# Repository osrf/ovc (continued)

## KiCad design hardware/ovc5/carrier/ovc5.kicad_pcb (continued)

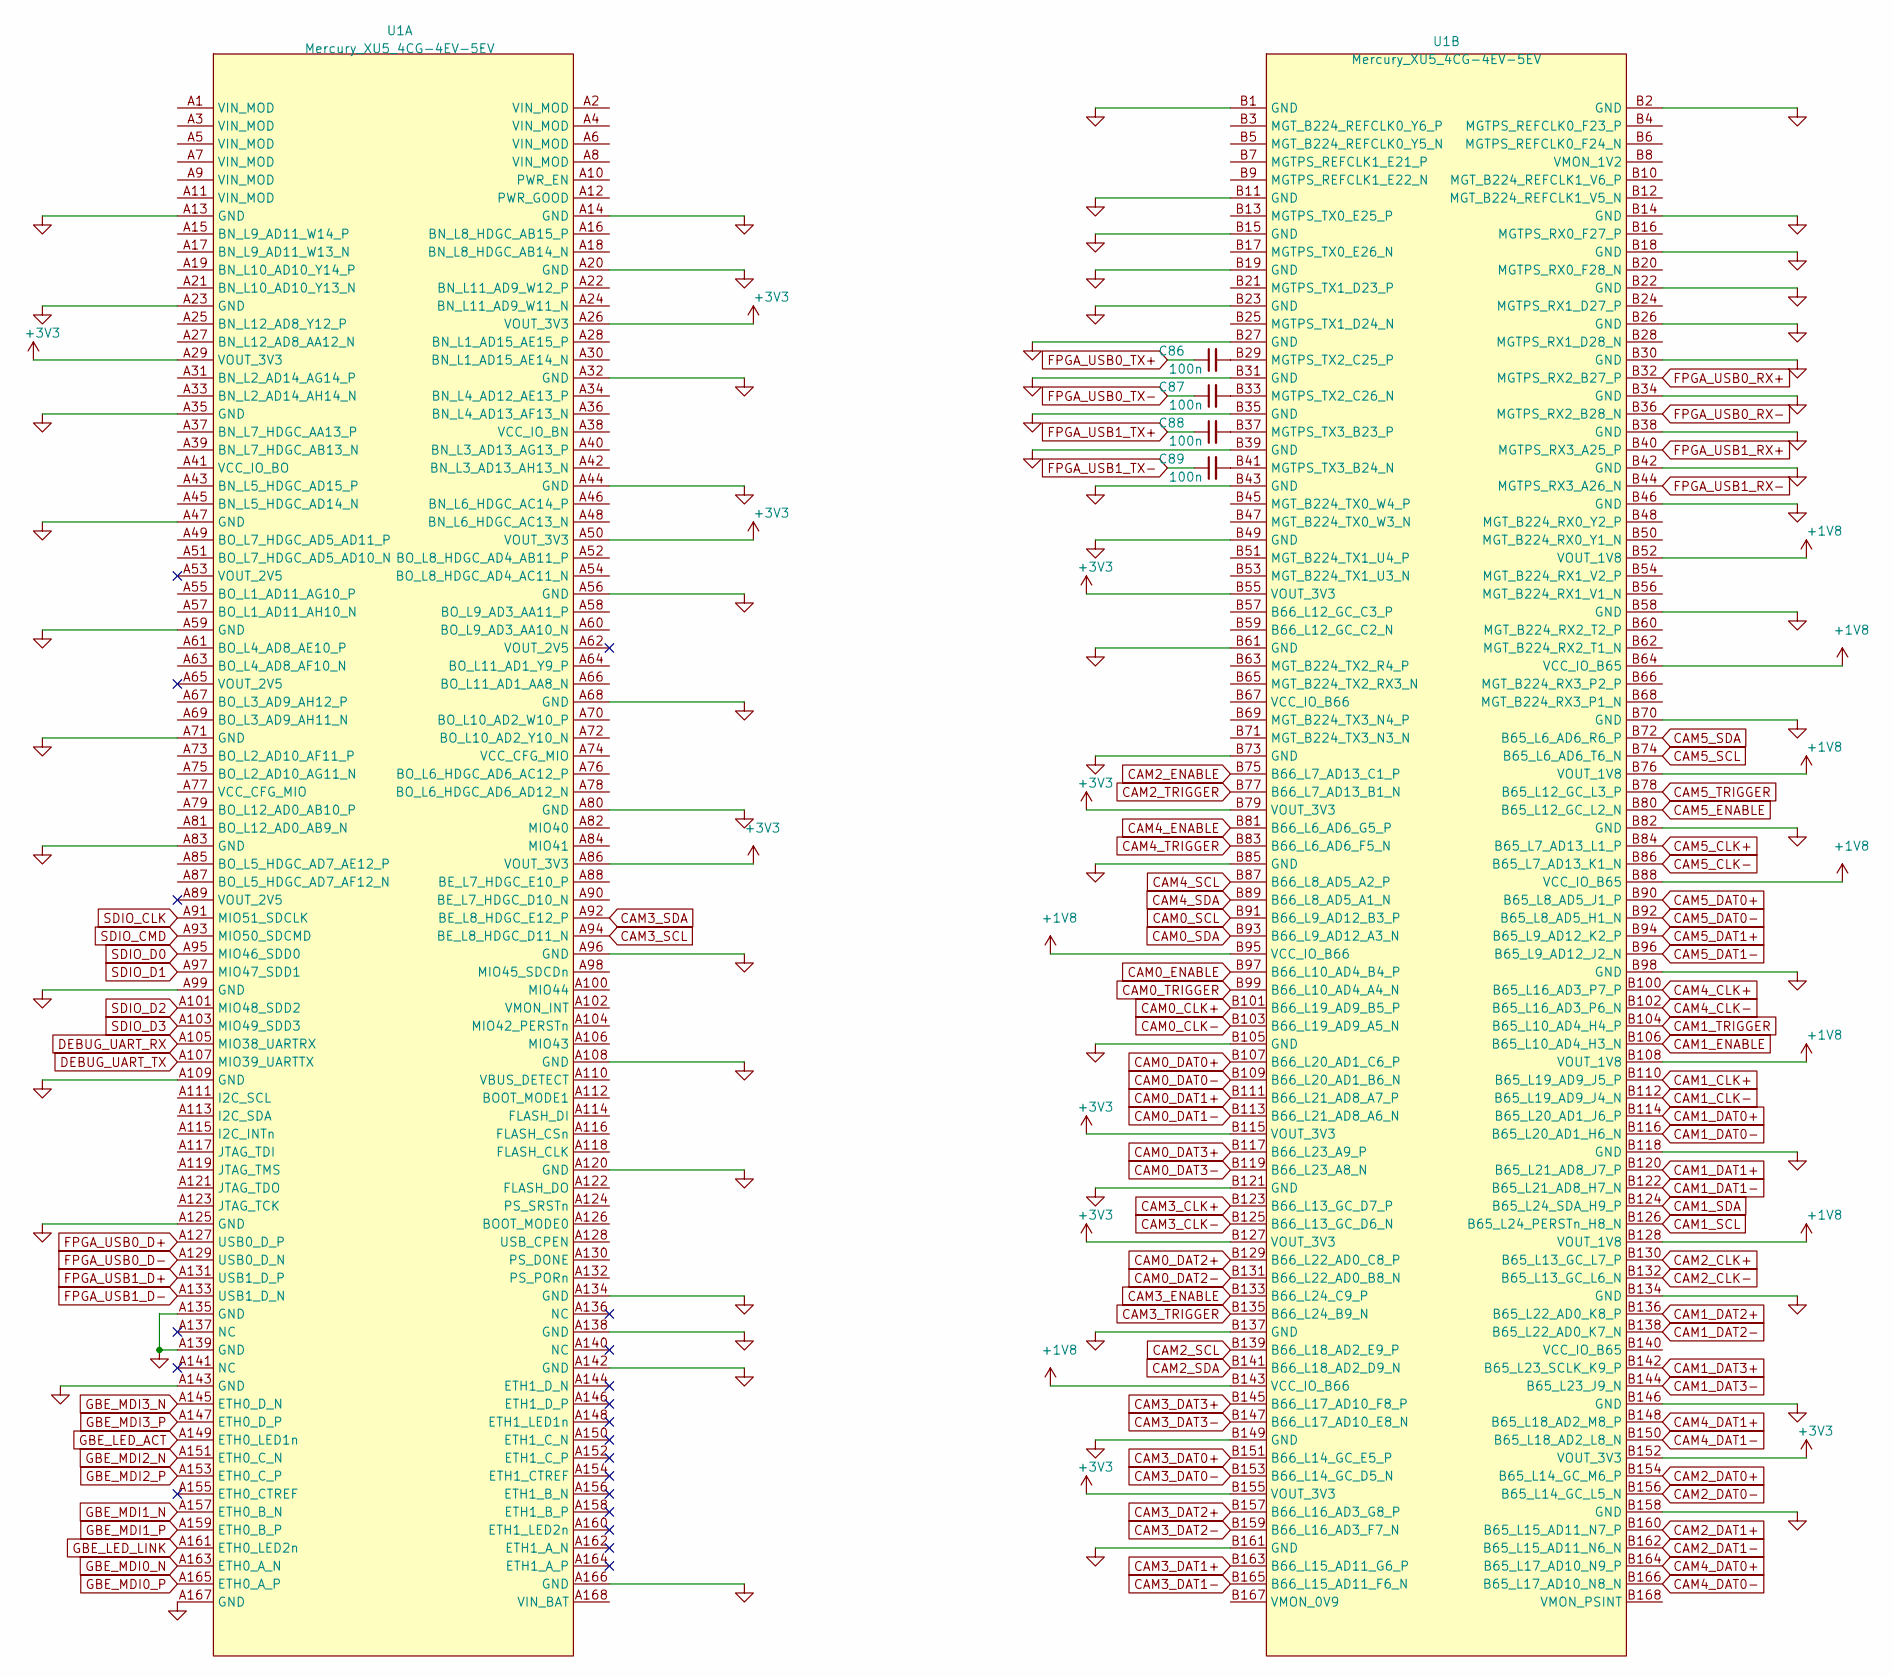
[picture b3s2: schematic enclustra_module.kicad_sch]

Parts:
C86, C87, C88, C89: 100n; C_0402_1005Metric
U1: Mercury_XU5_4CG-4EV-5EV; Mercury_XU5

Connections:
+1V8: U1.B52 (VOUT_1V8), U1.B64 (VCC_IO_B65), U1.B76 (VOUT_1V8), U1.B88 (VCC_IO_B65), U1.B95 (VCC_IO_B66), U1.B108 (VOUT_1V8), U1.B128 (VOUT_1V8), U1.B143 (VCC_IO_B66); also elsewhere on the board
+3V3: U1.A26 (VOUT_3V3), U1.A29 (VOUT_3V3), U1.A50 (VOUT_3V3), U1.A86 (VOUT_3V3), U1.B55 (VOUT_3V3), U1.B79 (VOUT_3V3), U1.B115 (VOUT_3V3), U1.B127 (VOUT_3V3), U1.B152 (VOUT_3V3), U1.B155 (VOUT_3V3); also elsewhere on the board
CAM0_CLK+: U1.B101 (B66_L19_AD9_B5_P); also elsewhere on the board
CAM0_CLK-: U1.B103 (B66_L19_AD9_A5_N); also elsewhere on the board
CAM0_DAT0+: U1.B107 (B66_L20_AD1_C6_P); also elsewhere on the board
CAM0_DAT0-: U1.B109 (B66_L20_AD1_B6_N); also elsewhere on the board
CAM0_DAT1+: U1.B111 (B66_L21_AD8_A7_P); also elsewhere on the board
CAM0_DAT1-: U1.B113 (B66_L21_AD8_A6_N); also elsewhere on the board
CAM0_DAT2+: U1.B129 (B66_L22_AD0_C8_P); also elsewhere on the board
CAM0_DAT2-: U1.B131 (B66_L22_AD0_B8_N); also elsewhere on the board
CAM0_DAT3+: U1.B117 (B66_L23_A9_P); also elsewhere on the board
CAM0_DAT3-: U1.B119 (B66_L23_A8_N); also elsewhere on the board
CAM0_ENABLE: U1.B97 (B66_L10_AD4_B4_P); also elsewhere on the board
CAM0_SCL: U1.B91 (B66_L9_AD12_B3_P); also elsewhere on the board
CAM0_SDA: U1.B93 (B66_L9_AD12_A3_N); also elsewhere on the board
CAM0_TRIGGER: U1.B99 (B66_L10_AD4_A4_N); also elsewhere on the board
CAM1_CLK+: U1.B110 (B65_L19_AD9_J5_P); also elsewhere on the board
CAM1_CLK-: U1.B112 (B65_L19_AD9_J4_N); also elsewhere on the board
CAM1_DAT0+: U1.B114 (B65_L20_AD1_J6_P); also elsewhere on the board
CAM1_DAT0-: U1.B116 (B65_L20_AD1_H6_N); also elsewhere on the board
CAM1_DAT1+: U1.B120 (B65_L21_AD8_J7_P); also elsewhere on the board
CAM1_DAT1-: U1.B122 (B65_L21_AD8_H7_N); also elsewhere on the board
CAM1_DAT2+: U1.B136 (B65_L22_AD0_K8_P); also elsewhere on the board
CAM1_DAT2-: U1.B138 (B65_L22_AD0_K7_N); also elsewhere on the board
CAM1_DAT3+: U1.B142 (B65_L23_SCLK_K9_P); also elsewhere on the board
CAM1_DAT3-: U1.B144 (B65_L23_J9_N); also elsewhere on the board
CAM1_ENABLE: U1.B106 (B65_L10_AD4_H3_N); also elsewhere on the board
CAM1_SCL: U1.B126 (B65_L24_PERSTn_H8_N); also elsewhere on the board
CAM1_SDA: U1.B124 (B65_L24_SDA_H9_P); also elsewhere on the board
CAM1_TRIGGER: U1.B104 (B65_L10_AD4_H4_P); also elsewhere on the board
CAM2_CLK+: U1.B130 (B65_L13_GC_L7_P); also elsewhere on the board
CAM2_CLK-: U1.B132 (B65_L13_GC_L6_N); also elsewhere on the board
CAM2_DAT0+: U1.B154 (B65_L14_GC_M6_P); also elsewhere on the board
CAM2_DAT0-: U1.B156 (B65_L14_GC_L5_N); also elsewhere on the board
CAM2_DAT1+: U1.B160 (B65_L15_AD11_N7_P); also elsewhere on the board
CAM2_DAT1-: U1.B162 (B65_L15_AD11_N6_N); also elsewhere on the board
CAM2_ENABLE: U1.B75 (B66_L7_AD13_C1_P); also elsewhere on the board
CAM2_SCL: U1.B139 (B66_L18_AD2_E9_P); also elsewhere on the board
CAM2_SDA: U1.B141 (B66_L18_AD2_D9_N); also elsewhere on the board
CAM2_TRIGGER: U1.B77 (B66_L7_AD13_B1_N); also elsewhere on the board
CAM3_CLK+: U1.B123 (B66_L13_GC_D7_P); also elsewhere on the board
CAM3_CLK-: U1.B125 (B66_L13_GC_D6_N); also elsewhere on the board
CAM3_DAT0+: U1.B151 (B66_L14_GC_E5_P); also elsewhere on the board
CAM3_DAT0-: U1.B153 (B66_L14_GC_D5_N); also elsewhere on the board
CAM3_DAT1+: U1.B163 (B66_L15_AD11_G6_P); also elsewhere on the board
CAM3_DAT1-: U1.B165 (B66_L15_AD11_F6_N); also elsewhere on the board
CAM3_DAT2+: U1.B157 (B66_L16_AD3_G8_P); also elsewhere on the board
CAM3_DAT2-: U1.B159 (B66_L16_AD3_F7_N); also elsewhere on the board
CAM3_DAT3+: U1.B145 (B66_L17_AD10_F8_P); also elsewhere on the board
CAM3_DAT3-: U1.B147 (B66_L17_AD10_E8_N); also elsewhere on the board
CAM3_ENABLE: U1.B133 (B66_L24_C9_P); also elsewhere on the board
CAM3_SCL: U1.A94 (BE_L8_HDGC_D11_N); also elsewhere on the board
CAM3_SDA: U1.A92 (BE_L8_HDGC_E12_P); also elsewhere on the board
CAM3_TRIGGER: U1.B135 (B66_L24_B9_N); also elsewhere on the board
CAM4_CLK+: U1.B100 (B65_L16_AD3_P7_P); also elsewhere on the board
CAM4_CLK-: U1.B102 (B65_L16_AD3_P6_N); also elsewhere on the board
CAM4_DAT0+: U1.B164 (B65_L17_AD10_N9_P); also elsewhere on the board
CAM4_DAT0-: U1.B166 (B65_L17_AD10_N8_N); also elsewhere on the board
CAM4_DAT1+: U1.B148 (B65_L18_AD2_M8_P); also elsewhere on the board
CAM4_DAT1-: U1.B150 (B65_L18_AD2_L8_N); also elsewhere on the board
CAM4_ENABLE: U1.B81 (B66_L6_AD6_G5_P); also elsewhere on the board
CAM4_SCL: U1.B87 (B66_L8_AD5_A2_P); also elsewhere on the board
CAM4_SDA: U1.B89 (B66_L8_AD5_A1_N); also elsewhere on the board
CAM4_TRIGGER: U1.B83 (B66_L6_AD6_F5_N); also elsewhere on the board
CAM5_CLK+: U1.B84 (B65_L7_AD13_L1_P); also elsewhere on the board
CAM5_CLK-: U1.B86 (B65_L7_AD13_K1_N); also elsewhere on the board
CAM5_DAT0+: U1.B90 (B65_L8_AD5_J1_P); also elsewhere on the board
CAM5_DAT0-: U1.B92 (B65_L8_AD5_H1_N); also elsewhere on the board
CAM5_DAT1+: U1.B94 (B65_L9_AD12_K2_P); also elsewhere on the board
CAM5_DAT1-: U1.B96 (B65_L9_AD12_J2_N); also elsewhere on the board
CAM5_ENABLE: U1.B80 (B65_L12_GC_L2_N); also elsewhere on the board
CAM5_SCL: U1.B74 (B65_L6_AD6_T6_N); also elsewhere on the board
CAM5_SDA: U1.B72 (B65_L6_AD6_R6_P); also elsewhere on the board
CAM5_TRIGGER: U1.B78 (B65_L12_GC_L3_P); also elsewhere on the board
DEBUG_UART_RX: U1.A105 (MIO38_UARTRX); also elsewhere on the board
DEBUG_UART_TX: U1.A107 (MIO39_UARTTX); also elsewhere on the board
FPGA_USB0_D+: U1.A127 (USB0_D_P); also elsewhere on the board
FPGA_USB0_D-: U1.A129 (USB0_D_N); also elsewhere on the board
FPGA_USB0_RX+: U1.B32 (MGTPS_RX2_B27_P); also elsewhere on the board
FPGA_USB0_RX-: U1.B36 (MGTPS_RX2_B28_N); also elsewhere on the board
FPGA_USB0_TX+: C86.1; also elsewhere on the board
FPGA_USB0_TX-: C87.1; also elsewhere on the board
FPGA_USB1_D+: U1.A131 (USB1_D_P); also elsewhere on the board
FPGA_USB1_D-: U1.A133 (USB1_D_N); also elsewhere on the board
FPGA_USB1_RX+: U1.B40 (MGTPS_RX3_A25_P); also elsewhere on the board
FPGA_USB1_RX-: U1.B44 (MGTPS_RX3_A26_N); also elsewhere on the board
FPGA_USB1_TX+: C88.1; also elsewhere on the board
FPGA_USB1_TX-: C89.1; also elsewhere on the board
GBE_LED_ACT: U1.A149 (ETH0_LED1n); also elsewhere on the board
GBE_LED_LINK: U1.A161 (ETH0_LED2n); also elsewhere on the board
GBE_MDI0_N: U1.A163 (ETH0_A_N); also elsewhere on the board
GBE_MDI0_P: U1.A165 (ETH0_A_P); also elsewhere on the board
GBE_MDI1_N: U1.A157 (ETH0_B_N); also elsewhere on the board
GBE_MDI1_P: U1.A159 (ETH0_B_P); also elsewhere on the board
GBE_MDI2_N: U1.A151 (ETH0_C_N); also elsewhere on the board
GBE_MDI2_P: U1.A153 (ETH0_C_P); also elsewhere on the board
GBE_MDI3_N: U1.A145 (ETH0_D_N); also elsewhere on the board
GBE_MDI3_P: U1.A147 (ETH0_D_P); also elsewhere on the board
GND: U1.A13 (GND), U1.A14 (GND), U1.A20 (GND), U1.A23 (GND), U1.A32 (GND), U1.A35 (GND), U1.A44 (GND), U1.A47 (GND), U1.A56 (GND), U1.A59 (GND), U1.A68 (GND), U1.A71 (GND), U1.A80 (GND), U1.A83 (GND), U1.A96 (GND), U1.A99 (GND), U1.A108 (GND), U1.A109 (GND), U1.A120 (GND), U1.A125 (GND), U1.A134 (GND), U1.A135 (GND), U1.A138 (GND), U1.A139 (GND), U1.A142 (GND), U1.A143 (GND), U1.A166 (GND), U1.A167 (GND), U1.B1 (GND), U1.B2 (GND), U1.B11 (GND), U1.B14 (GND), U1.B15 (GND), U1.B18 (GND), U1.B19 (GND), U1.B22 (GND), U1.B23 (GND), U1.B26 (GND), U1.B27 (GND), U1.B30 (GND), U1.B31 (GND), U1.B34 (GND), U1.B35 (GND), U1.B38 (GND), U1.B39 (GND), U1.B42 (GND), U1.B43 (GND), U1.B46 (GND), U1.B49 (GND), U1.B58 (GND), U1.B61 (GND), U1.B70 (GND), U1.B73 (GND), U1.B82 (GND), U1.B85 (GND), U1.B98 (GND), U1.B105 (GND), U1.B118 (GND), U1.B121 (GND), U1.B134 (GND), U1.B137 (GND), U1.B146 (GND), U1.B149 (GND), U1.B158 (GND), U1.B161 (GND); also elsewhere on the board
unnamed: C86.2, U1.B29 (MGTPS_TX2_C25_P)
unnamed: C87.2, U1.B33 (MGTPS_TX2_C26_N)
unnamed: C88.2, U1.B37 (MGTPS_TX3_B23_P)
unnamed: C89.2, U1.B41 (MGTPS_TX3_B24_N)
SDIO_CLK: U1.A91 (MIO51_SDCLK); also elsewhere on the board
SDIO_CMD: U1.A93 (MIO50_SDCMD); also elsewhere on the board
SDIO_D0: U1.A95 (MIO46_SDD0); also elsewhere on the board
SDIO_D1: U1.A97 (MIO47_SDD1); also elsewhere on the board
SDIO_D2: U1.A101 (MIO48_SDD2); also elsewhere on the board
SDIO_D3: U1.A103 (MIO49_SDD3); also elsewhere on the board

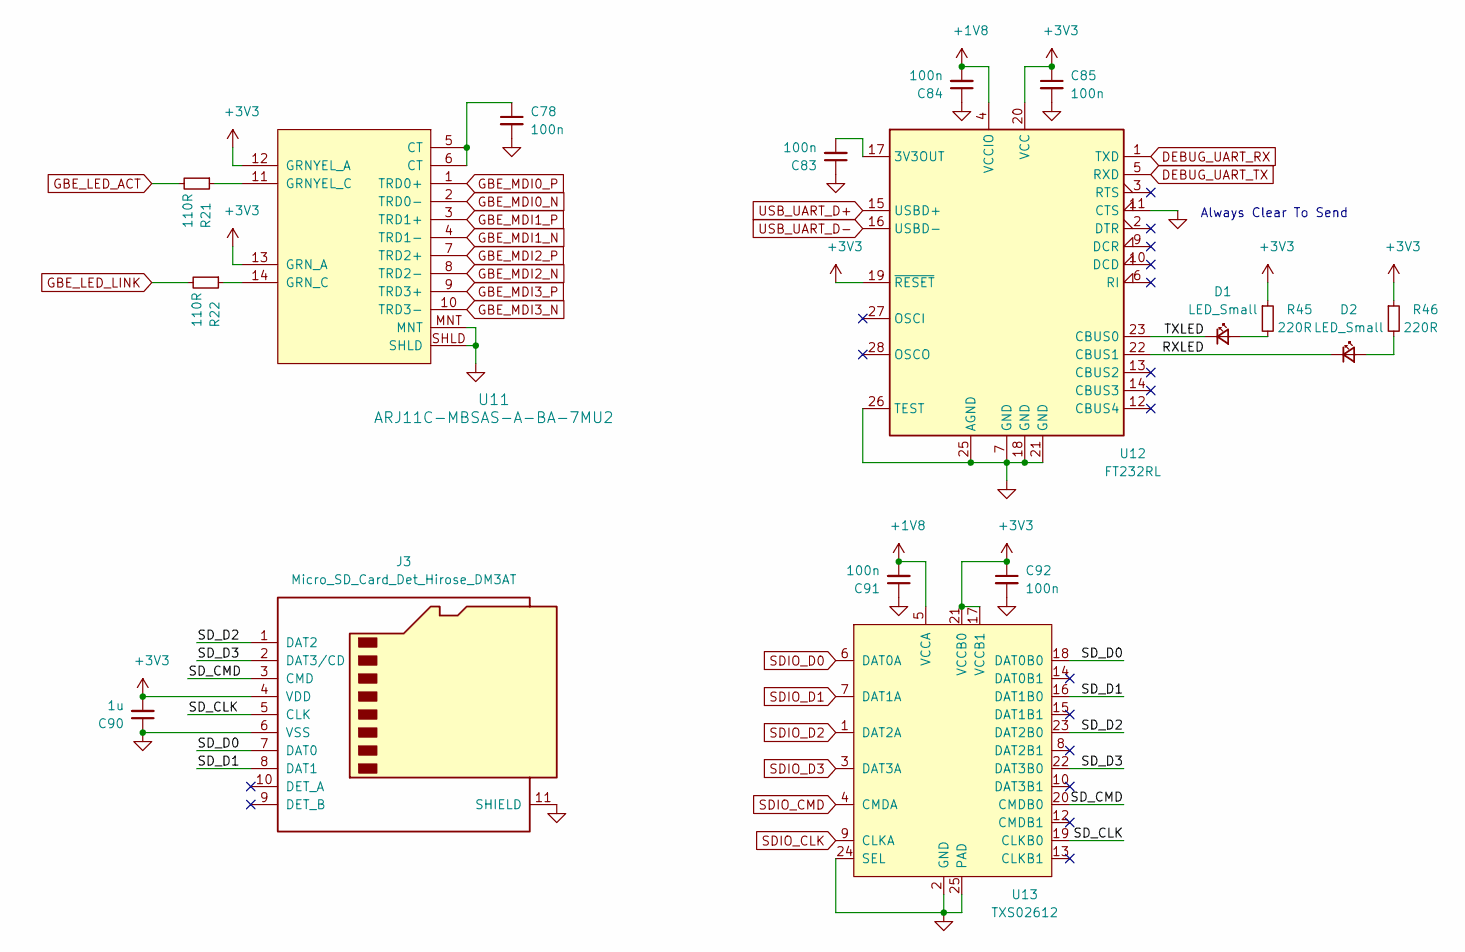
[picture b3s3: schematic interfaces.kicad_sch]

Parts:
C78, C83, C84, C85, C91, C92: 100n; C_0402_1005Metric
C90: 1u; C_0402_1005Metric
D1, D2: LED_Small; LED_0402_1005Metric
J3: Micro_SD_Card_Det_Hirose_DM3AT; microSD_HC_Hirose_DM3AT-SF-PEJM5
R21, R22: 110R; R_0603_1608Metric
R45, R46: 220R; R_0402_1005Metric
U11: ARJ11C-MBSAS-A-BA-7MU2
U12: FT232RL; SSOP-28_5.3x10.2mm_P0.65mm
U13: TXS02612; TI_RTW0024B

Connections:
+1V8: C84.2, C91.2, U12.4 (VCCIO), U13.5 (VCCA); also elsewhere on the board
+3V3: C85.1, C90.2, C92.1, J3.4 (VDD), R45.1, R46.1, U11.12 (GRNYEL_A), U11.13 (GRN_A), U12.19 (~RESET~), U12.20 (VCC), U13.17 (VCCB1), U13.21 (VCCB0); also elsewhere on the board
/Interfaces/RXLED: D2.1 (K), U12.22 (CBUS1)
/Interfaces/SD_CLK: J3.5 (CLK), U13.19 (CLKB0)
/Interfaces/SD_CMD: J3.3 (CMD), U13.20 (CMDB0)
/Interfaces/SD_D0: J3.7 (DAT0), U13.18 (DAT0B0)
/Interfaces/SD_D1: J3.8 (DAT1), U13.16 (DAT1B0)
/Interfaces/SD_D2: J3.1 (DAT2), U13.23 (DAT2B0)
/Interfaces/SD_D3: J3.2 (DAT3/CD), U13.22 (DAT3B0)
/Interfaces/TXLED: D1.1 (K), U12.23 (CBUS0)
DEBUG_UART_RX: U12.1 (TXD); also elsewhere on the board
DEBUG_UART_TX: U12.5 (RXD); also elsewhere on the board
GBE_LED_ACT: R21.2; also elsewhere on the board
GBE_LED_LINK: R22.2; also elsewhere on the board
GBE_MDI0_N: U11.2 (TRD0-); also elsewhere on the board
GBE_MDI0_P: U11.1 (TRD0+); also elsewhere on the board
GBE_MDI1_N: U11.4 (TRD1-); also elsewhere on the board
GBE_MDI1_P: U11.3 (TRD1+); also elsewhere on the board
GBE_MDI2_N: U11.8 (TRD2-); also elsewhere on the board
GBE_MDI2_P: U11.7 (TRD2+); also elsewhere on the board
GBE_MDI3_N: U11.10 (TRD3-); also elsewhere on the board
GBE_MDI3_P: U11.9 (TRD3+); also elsewhere on the board
GND: C78.2, C83.1, C84.1, C85.2, C90.1, C91.1, C92.2, J3.6 (VSS), J3.11 (SHIELD), U11.MNT, U11.SHLD, U12.7 (GND), U12.11 (CTS), U12.18 (GND), U12.21 (GND), U12.25 (AGND), U12.26 (TEST), U13.2 (GND), U13.11 (GND), U13.24 (SEL), U13.25 (PAD); also elsewhere on the board
unnamed: C78.1, U11.5 (CT), U11.6 (CT)
unnamed: C83.2, U12.17 (3V3OUT)
unnamed: D1.2 (A), R45.2
unnamed: D2.2 (A), R46.2
unnamed: R21.1, U11.11 (GRNYEL_C)
unnamed: R22.1, U11.14 (GRN_C)
SDIO_CLK: U13.9 (CLKA); also elsewhere on the board
SDIO_CMD: U13.4 (CMDA); also elsewhere on the board
SDIO_D0: U13.6 (DAT0A); also elsewhere on the board
SDIO_D1: U13.7 (DAT1A); also elsewhere on the board
SDIO_D2: U13.1 (DAT2A); also elsewhere on the board
SDIO_D3: U13.3 (DAT3A); also elsewhere on the board
USB_UART_D+: U12.15 (USBD+); also elsewhere on the board
USB_UART_D-: U12.16 (USBD-); also elsewhere on the board

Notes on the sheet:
Always Clear To Send

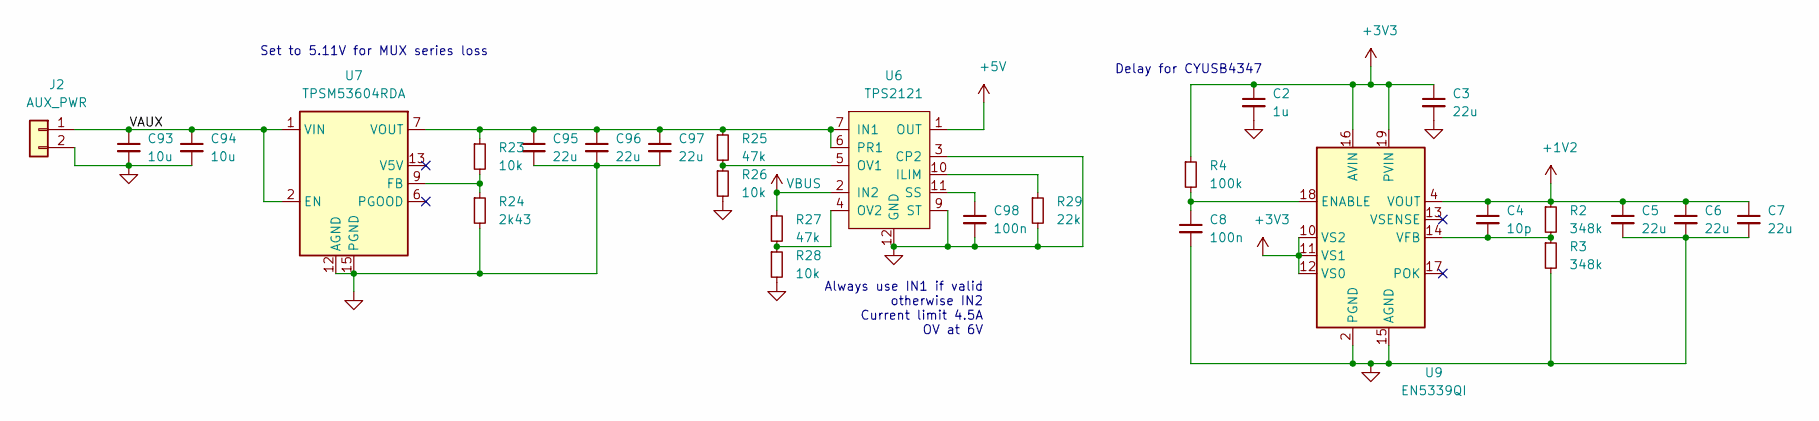
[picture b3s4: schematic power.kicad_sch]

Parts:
C2: 1u; C_0402_1005Metric
C3, C5, C6, C7, C95, C96, C97: 22u; C_0603_1608Metric
C4: 10p; C_0402_1005Metric
C8, C98: 100n; C_0402_1005Metric
C93, C94: 10u; C_1206_3216Metric
J2: AUX_PWR; Molex_Nano-Fit_105313-xx02_1x02_P2.50mm_Horizontal
R2, R3: 348k; R_0402_1005Metric
R4: 100k; R_0402_1005Metric
R23, R26, R28: 10k; R_0402_1005Metric
R24: 2k43; R_0402_1005Metric
R25, R27: 47k; R_0402_1005Metric
R29: 22k; R_0402_1005Metric
U6: TPS2121; Texas_VQFN-HR-12_2x2.5_Pitch0.5mm
U7: TPSM53604RDA; Texas_B3QFN-14-1EP_5x5.5mm_P0.65mm_ThermalVia
U9: EN5339QI; Converter_DCDC_Intel_QFN-24_4x6mm_P0.65mm_ThermalVias

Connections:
+1V2: C4.1, C5.1, C6.1, C7.1, R2.1, U9.4 (VOUT), U9.5 (VOUT), U9.6 (VOUT), U9.7 (VOUT); also elsewhere on the board
+3V3: C2.1, C3.1, R4.1, U9.10 (VS2), U9.11 (VS1), U9.12 (VS0), U9.16 (AVIN), U9.19 (PVIN), U9.20 (PVIN); also elsewhere on the board
+5V: U6.1 (OUT), U6.8 (OUT); also elsewhere on the board
/Power/VAUX: C93.1, C94.1, J2.1, U7.1 (VIN), U7.2 (EN), U7.14 (VIN)
GND: C2.2, C3.2, C5.2, C6.2, C7.2, C8.2, C93.2, C94.2, C95.2, C96.2, C97.2, C98.2, J2.2, R3.2, R24.2, R26.2, R28.2, R29.2, U6.3 (CP2), U6.9 (ST), U6.12 (GND), U7.3 (PGND), U7.10 (PGND), U7.11 (PGND), U7.12 (AGND), U7.15 (PGND), U9.2 (PGND), U9.3 (PGND), U9.8 (PGND), U9.9 (PGND), U9.15 (AGND), U9.25 (PGND); also elsewhere on the board
unnamed: C4.2, R2.2, R3.1, U9.14 (VFB)
unnamed: C8.1, R4.2, U9.18 (ENABLE)
unnamed: C95.1, C96.1, C97.1, R23.1, R25.1, U6.6 (PR1), U6.7 (IN1), U7.7 (VOUT), U7.8 (VOUT)
unnamed: C98.1, U6.11 (SS)
unnamed: R23.2, R24.1, U7.9 (FB)
unnamed: R25.2, R26.1, U6.5 (OV1)
unnamed: R27.2, R28.1, U6.4 (OV2)
unnamed: R29.1, U6.10 (ILIM)
VBUS: R27.1, U6.2 (IN2); also elsewhere on the board

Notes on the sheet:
Set to 5.11V for MUX series loss
Always use IN1 if valid otherwise IN2 Current limit 4.5A OV at 6V
Delay for CYUSB4347

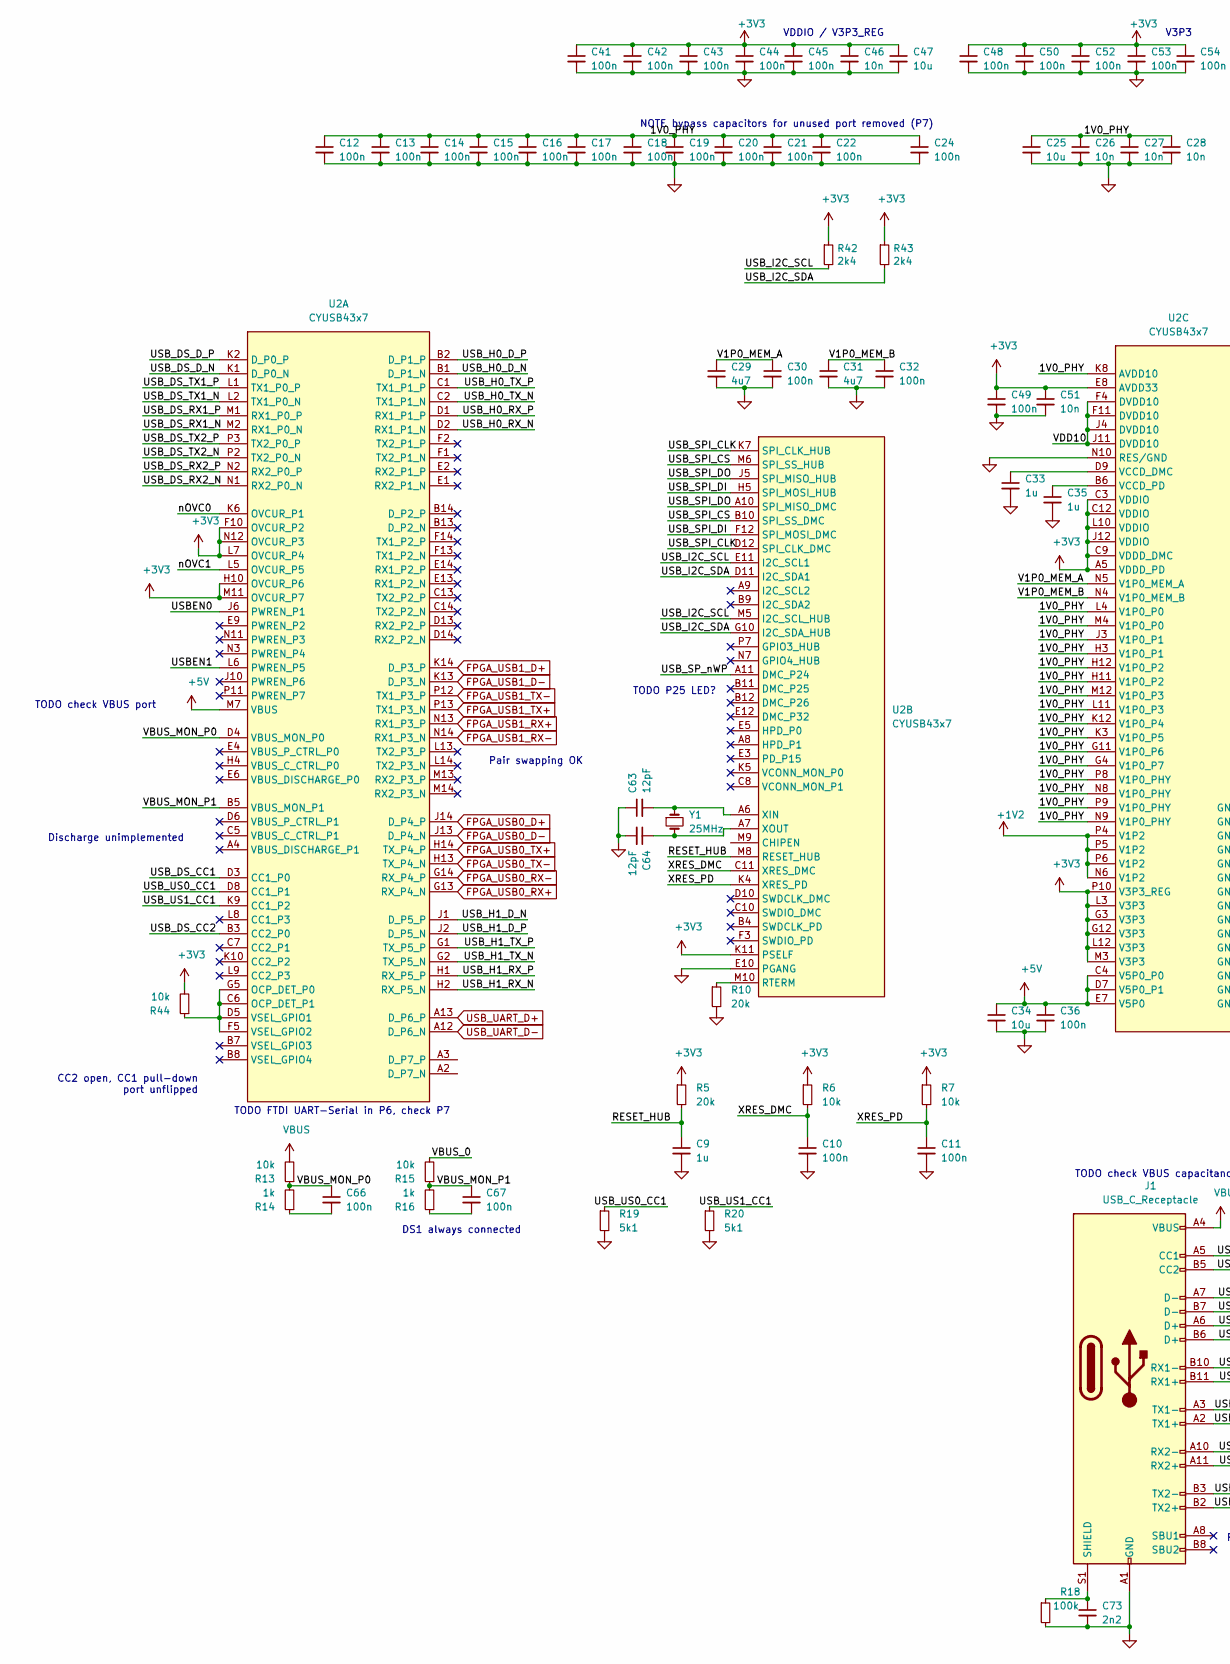
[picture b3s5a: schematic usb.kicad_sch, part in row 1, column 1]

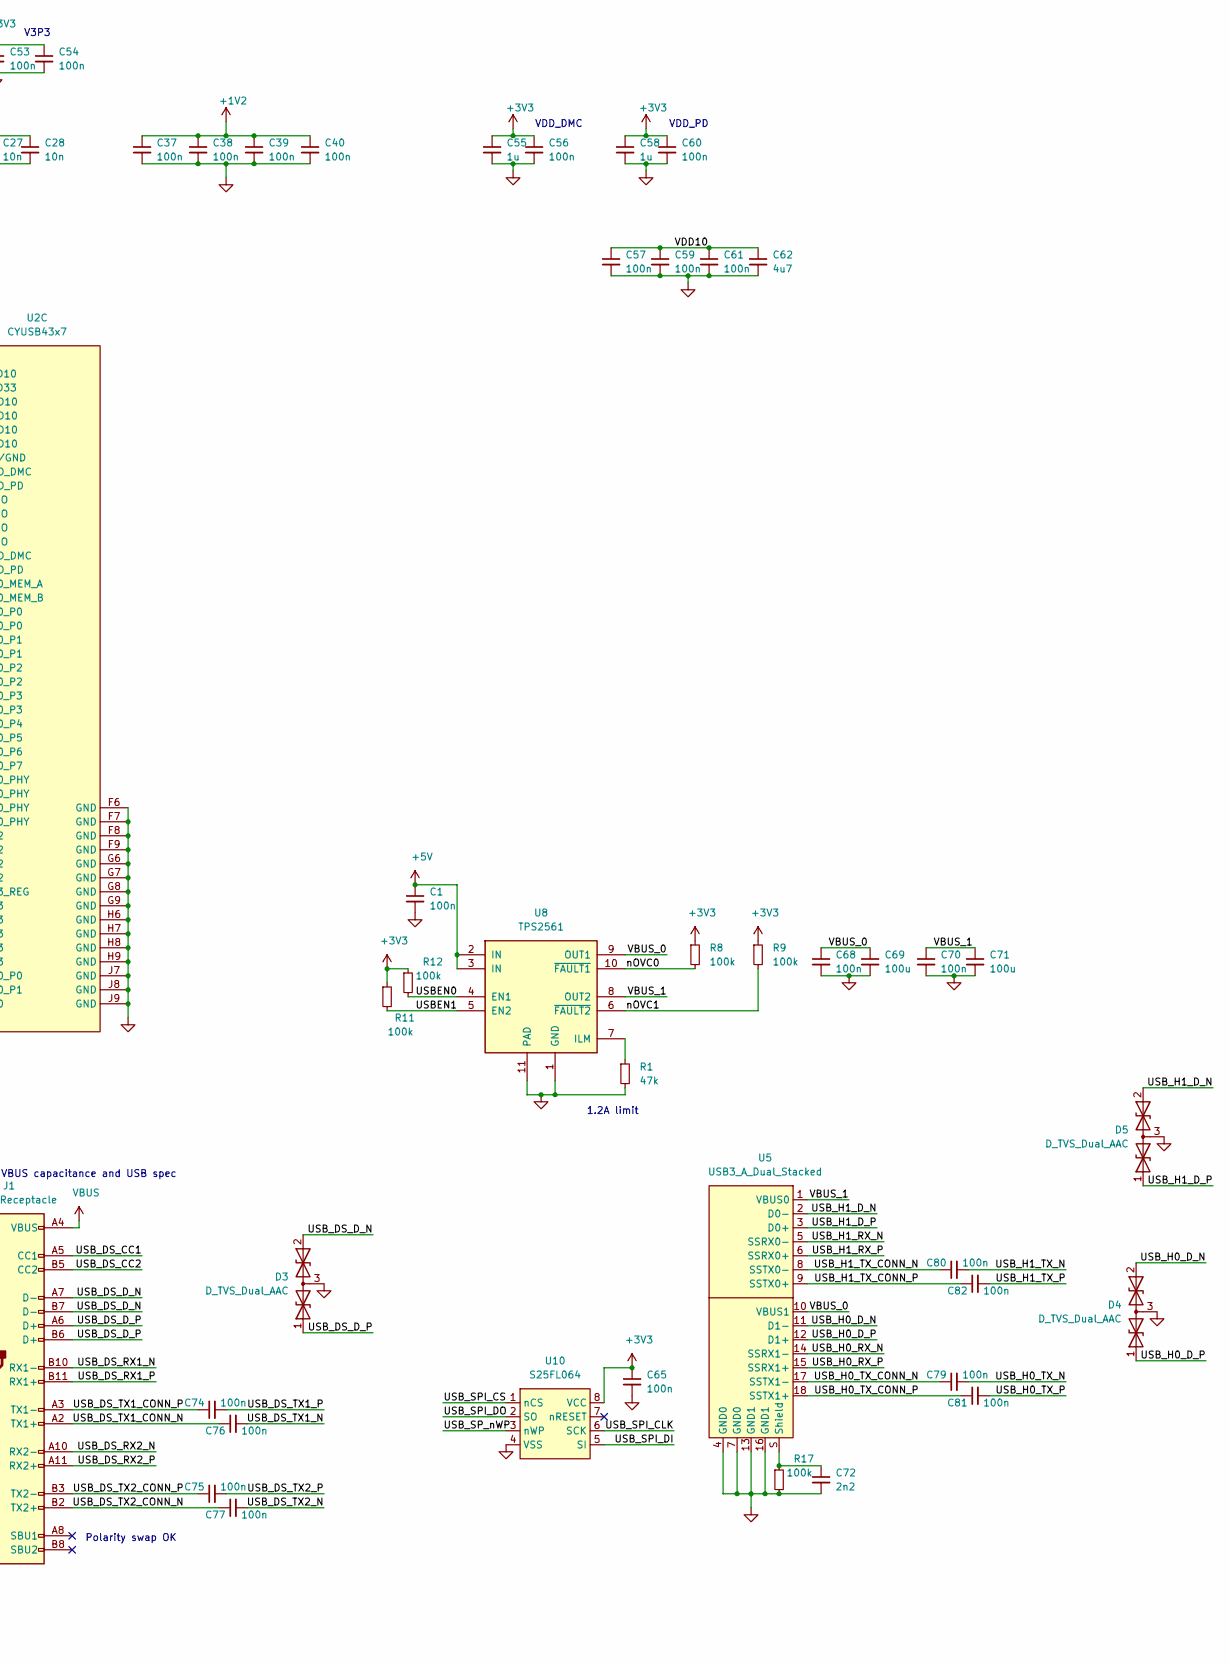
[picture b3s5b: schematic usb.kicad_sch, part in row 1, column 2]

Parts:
C1, C10, C11, C12, C13, C14, C15, C16, C17, C18, C19, C20, C21, C22, C24, C30, C32, C36, C37, C38, C39, C40, C41, C42, C43, C44, C45, C48, C49, C50, C52, C53, C54, C56, C57, C59, C60, C61, C65, C66, C67, C68, C70, C74, C75, C76, C77, C79, C80, C81, C82: 100n; C_0402_1005Metric
C9, C33, C35, C55, C58: 1u; C_0402_1005Metric
C25, C34, C47: 10u; C_0402_1005Metric
C26, C27, C28, C46, C51: 10n; C_0402_1005Metric
C29, C31, C62: 4u7; C_0402_1005Metric
C63, C64: 12pF; C_0402_1005Metric
C69, C71: 100u; C_1206_3216Metric
C72, C73: 2n2; C_0402_1005Metric
D3, D4, D5: D_TVS_Dual_AAC; TPD2EUSB30x
J1: USB_C_Receptacle; USB_C_Receptacle_Wurth_632723300011
R1: 47k; R_0402_1005Metric
R5, R10: 20k; R_0402_1005Metric
R6, R7, R13, R15, R44: 10k; R_0402_1005Metric
R8, R9, R11, R12, R17, R18: 100k; R_0402_1005Metric
R14, R16: 1k; R_0402_1005Metric
R19, R20: 5k1; R_0402_1005Metric
R42, R43: 2k4; R_0402_1005Metric; MPN ERA-2AED242X
U2: CYUSB43x7; BGA-192_14x14_12.0x12.0mm
U5: USB3_A_Dual_Stacked
U8: TPS2561; VSON-10-1EP_3x3mm_P0.5mm_EP1.65x2.4mm_ThermalVias
U10: S25FL064; WSON-8-1EP_6x5mm_P1.27mm_EP3.4x4mm
Y1: 25MHz; Crystal_SMD_2016-4Pin_2.0x1.6mm

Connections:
+1V2: C37.1, C38.1, C39.1, C40.1, U2.N6 (V1P2), U2.P4 (V1P2), U2.P5 (V1P2), U2.P6 (V1P2); also elsewhere on the board
+3V3: C41.1, C42.1, C43.1, C44.1, C45.1, C46.1, C47.1, C48.1, C49.1, C50.1, C51.1, C52.1, C53.1, C54.1, C55.1, C56.1, C58.1, C60.1, C65.1, R5.1, R6.1, R7.1, R8.1, R9.1, R11.1, R12.1, R42.1, R43.1, R44.2, U2.A5 (VDDD_PD), U2.C3 (VDDIO), U2.C9 (VDDD_DMC), U2.C12 (VDDIO), U2.E8 (AVDD33), U2.F10 (OVCUR_P2), U2.G3 (V3P3), U2.G12 (V3P3), U2.H10 (OVCUR_P6), U2.J12 (VDDIO), U2.K11 (PSELF), U2.L3 (V3P3), U2.L7 (OVCUR_P4), U2.L10 (VDDIO), U2.L12 (V3P3), U2.M3 (V3P3), U2.M11 (OVCUR_P7), U2.N12 (OVCUR_P3), U2.P10 (V3P3_REG), U10.8 (VCC); also elsewhere on the board
+5V: C1.1, C34.1, C36.1, U2.C4 (V5P0_P0), U2.D7 (V5P0_P1), U2.E7 (V5P0), U2.M7 (VBUS), U8.2 (IN), U8.3 (IN); also elsewhere on the board
/USB/1V0_PHY: C12.1, C13.1, C14.1, C15.1, C16.1, C17.1, C18.1, C19.1, C20.1, C21.1, C22.1, C24.1, C25.1, C26.1, C27.1, C28.1, U2.G4 (V1P0_P7), U2.G11 (V1P0_P6), U2.H3 (V1P0_P1), U2.H11 (V1P0_P2), U2.H12 (V1P0_P2), U2.J3 (V1P0_P1), U2.K3 (V1P0_P5), U2.K8 (AVDD10), U2.K12 (V1P0_P4), U2.L4 (V1P0_P0), U2.L11 (V1P0_P3), U2.M4 (V1P0_P0), U2.M12 (V1P0_P3), U2.N8 (V1P0_PHY), U2.N9 (V1P0_PHY), U2.P8 (V1P0_PHY), U2.P9 (V1P0_PHY)
/USB/RESET_HUB: C9.1, R5.2, U2.M8 (RESET_HUB)
/USB/USBEN0: R12.2, U2.J6 (PWREN_P1), U8.4 (EN1)
/USB/USBEN1: R11.2, U2.L6 (PWREN_P5), U8.5 (EN2)
/USB/USB_DS_CC1: J1.A5 (CC1), U2.D3 (CC1_P0)
/USB/USB_DS_CC2: J1.B5 (CC2), U2.B3 (CC2_P0)
/USB/USB_DS_D_N: D3.2 (A2), J1.A7 (D-), J1.B7 (D-), U2.K1 (D_P0_N)
/USB/USB_DS_D_P: D3.1 (A1), J1.A6 (D+), J1.B6 (D+), U2.K2 (D_P0_P)
/USB/USB_DS_RX1_N: J1.B10 (RX1-), U2.M2 (RX1_P0_N)
/USB/USB_DS_RX1_P: J1.B11 (RX1+), U2.M1 (RX1_P0_P)
/USB/USB_DS_RX2_N: J1.A10 (RX2-), U2.N1 (RX2_P0_N)
/USB/USB_DS_RX2_P: J1.A11 (RX2+), U2.N2 (RX2_P0_P)
/USB/USB_DS_TX1_CONN_N: C76.1, J1.A2 (TX1+)
/USB/USB_DS_TX1_CONN_P: C74.1, J1.A3 (TX1-)
/USB/USB_DS_TX1_N: C76.2, U2.L2 (TX1_P0_N)
/USB/USB_DS_TX1_P: C74.2, U2.L1 (TX1_P0_P)
/USB/USB_DS_TX2_CONN_N: C77.1, J1.B2 (TX2+)
/USB/USB_DS_TX2_CONN_P: C75.1, J1.B3 (TX2-)
/USB/USB_DS_TX2_N: C77.2, U2.P2 (TX2_P0_N)
/USB/USB_DS_TX2_P: C75.2, U2.P3 (TX2_P0_P)
/USB/USB_H0_D_N: D4.2 (A2), U2.B1 (D_P1_N), U5.11 (D1-)
/USB/USB_H0_D_P: D4.1 (A1), U2.B2 (D_P1_P), U5.12 (D1+)
/USB/USB_H0_RX_N: U2.D2 (RX1_P1_N), U5.14 (SSRX1-)
/USB/USB_H0_RX_P: U2.D1 (RX1_P1_P), U5.15 (SSRX1+)
/USB/USB_H0_TX_CONN_N: C79.1, U5.17 (SSTX1-)
/USB/USB_H0_TX_CONN_P: C81.1, U5.18 (SSTX1+)
/USB/USB_H0_TX_N: C79.2, U2.C2 (TX1_P1_N)
/USB/USB_H0_TX_P: C81.2, U2.C1 (TX1_P1_P)
/USB/USB_H1_D_N: D5.2 (A2), U2.J1 (D_P5_P), U5.2 (D0-)
/USB/USB_H1_D_P: D5.1 (A1), U2.J2 (D_P5_N), U5.3 (D0+)
/USB/USB_H1_RX_N: U2.H2 (RX_P5_N), U5.5 (SSRX0-)
/USB/USB_H1_RX_P: U2.H1 (RX_P5_P), U5.6 (SSRX0+)
/USB/USB_H1_TX_CONN_N: C80.1, U5.8 (SSTX0-)
/USB/USB_H1_TX_CONN_P: C82.1, U5.9 (SSTX0+)
/USB/USB_H1_TX_N: C80.2, U2.G2 (TX_P5_N)
/USB/USB_H1_TX_P: C82.2, U2.G1 (TX_P5_P)
/USB/USB_I2C_SCL: R42.2, U2.E11 (I2C_SCL1), U2.M5 (I2C_SCL_HUB)
/USB/USB_I2C_SDA: R43.2, U2.D11 (I2C_SDA1), U2.G10 (I2C_SDA_HUB)
/USB/USB_SPI_CLK: U2.D12 (SPI_CLK_DMC), U2.K7 (SPI_CLK_HUB), U10.6 (SCK)
/USB/USB_SPI_CS: U2.B10 (SPI_SS_DMC), U2.M6 (SPI_SS_HUB), U10.1 (nCS)
/USB/USB_SPI_DI: U2.F12 (SPI_MOSI_DMC), U2.H5 (SPI_MOSI_HUB), U10.5 (SI)
/USB/USB_SPI_DO: U2.A10 (SPI_MISO_DMC), U2.J5 (SPI_MISO_HUB), U10.2 (SO)
/USB/USB_SP_nWP: U2.A11 (DMC_P24), U10.3 (nWP)
/USB/USB_US0_CC1: R19.1, U2.D8 (CC1_P1)
/USB/USB_US1_CC1: R20.1, U2.K9 (CC1_P2)
/USB/V1P0_MEM_A: C29.1, C30.1, U2.N5 (V1P0_MEM_A)
/USB/V1P0_MEM_B: C31.1, C32.1, U2.N4 (V1P0_MEM_B)
/USB/VBUS_0: C68.1, C69.1, R15.2, U5.10 (VBUS1), U8.9 (OUT1)
/USB/VBUS_1: C70.1, C71.1, U5.1 (VBUS0), U8.8 (OUT2)
/USB/VBUS_MON_P0: C66.1, R13.1, R14.2, U2.D4 (VBUS_MON_P0)
/USB/VBUS_MON_P1: C67.1, R15.1, R16.2, U2.B5 (VBUS_MON_P1)
/USB/VDD10: C57.1, C59.1, C61.1, C62.1, U2.F4 (DVDD10), U2.F11 (DVDD10), U2.J4 (DVDD10), U2.J11 (DVDD10)
/USB/XRES_DMC: C10.1, R6.2, U2.C11 (XRES_DMC)
/USB/XRES_PD: C11.1, R7.2, U2.K4 (XRES_PD)
/USB/nOVC0: R8.2, U2.K6 (OVCUR_P1), U8.10 (~FAULT1)
/USB/nOVC1: R9.2, U2.L5 (OVCUR_P5), U8.6 (~FAULT2)
FPGA_USB0_D+: U2.J14 (D_P4_P); also elsewhere on the board
FPGA_USB0_D-: U2.J13 (D_P4_N); also elsewhere on the board
FPGA_USB0_RX+: U2.G13 (RX_P4_N); also elsewhere on the board
FPGA_USB0_RX-: U2.G14 (RX_P4_P); also elsewhere on the board
FPGA_USB0_TX+: U2.H14 (TX_P4_P); also elsewhere on the board
FPGA_USB0_TX-: U2.H13 (TX_P4_N); also elsewhere on the board
FPGA_USB1_D+: U2.K14 (D_P3_P); also elsewhere on the board
FPGA_USB1_D-: U2.K13 (D_P3_N); also elsewhere on the board
FPGA_USB1_RX+: U2.N13 (RX1_P3_P); also elsewhere on the board
FPGA_USB1_RX-: U2.N14 (RX1_P3_N); also elsewhere on the board
FPGA_USB1_TX+: U2.P13 (TX1_P3_N); also elsewhere on the board
FPGA_USB1_TX-: U2.P12 (TX1_P3_P); also elsewhere on the board
GND: C1.2, C9.2, C10.2, C11.2, C12.2, C13.2, C14.2, C15.2, C16.2, C17.2, C18.2, C19.2, C20.2, C21.2, C22.2, C24.2, C25.2, C26.2, C27.2, C28.2, C29.2, C30.2, C31.2, C32.2, C33.2, C34.2, C35.2, C36.2, C37.2, C38.2, C39.2, C40.2, C41.2, C42.2, C43.2, C44.2, C45.2, C46.2, C47.2, C48.2, C49.2, C50.2, C51.2, C52.2, C53.2, C54.2, C55.2, C56.2, C57.2, C58.2, C59.2, C60.2, C61.2, C62.2, C63.1, C64.2, C65.2, C68.2, C69.2, C70.2, C71.2, C72.2, C73.2, D3.3 (common), D4.3 (common), D5.3 (common), J1.A1 (GND), J1.A12 (GND), J1.B1 (GND), J1.B12 (GND), R1.2, R10.2, R17.2, R18.2, R19.2, R20.2, U2.E10 (PGANG), U2.F6 (GND), U2.F7 (GND), U2.F8 (GND), U2.F9 (GND), U2.G6 (GND), U2.G7 (GND), U2.G8 (GND), U2.G9 (GND), U2.H6 (GND), U2.H7 (GND), U2.H8 (GND), U2.H9 (GND), U2.J7 (GND), U2.J8 (GND), U2.J9 (GND), U2.N10 (RES/GND), U5.4 (GND0), U5.7 (GND0), U5.13 (GND1), U5.16 (GND1), U8.1 (GND), U8.11 (PAD), U10.4 (VSS); also elsewhere on the board
unnamed: C33.1, U2.D9 (VCCD_DMC)
unnamed: C35.1, U2.B6 (VCCD_PD)
unnamed: C63.2, U2.A6 (XIN), Y1.1
unnamed: C64.1, U2.A7 (XOUT), Y1.2
unnamed: C66.2, R14.1
unnamed: C67.2, R16.1
unnamed: C72.1, R17.1, U5.S (Shield)
unnamed: C73.1, J1.S1 (SHIELD), R18.1
unnamed: R1.1, U8.7 (ILM)
unnamed: R10.1, U2.M10 (RTERM)
unnamed: R44.1, U2.C6 (OCP_DET_P1), U2.D5 (VSEL_GPIO1), U2.F5 (VSEL_GPIO2), U2.G5 (OCP_DET_P0)
USB_UART_D+: U2.A13 (D_P6_P); also elsewhere on the board
USB_UART_D-: U2.A12 (D_P6_N); also elsewhere on the board
VBUS: J1.A4 (VBUS), J1.A9 (VBUS), J1.B4 (VBUS), J1.B9 (VBUS), R13.2; also elsewhere on the board

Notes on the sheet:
TODO check VBUS port
Discharge unimplemented
CC2 open, CC1 pull-down port unflipped
DS1 always connected
TODO FTDI UART-Serial in P6, check P7
Pair swapping OK
NOTE bypass capacitors for unused port removed (P7)
TODO P25 LED?
VDDIO / V3P3_REG
V3P3
TODO check VBUS capacitance and USB spec
Polarity swap OK
VDD_DMC
1.2A limit
VDD_PD
